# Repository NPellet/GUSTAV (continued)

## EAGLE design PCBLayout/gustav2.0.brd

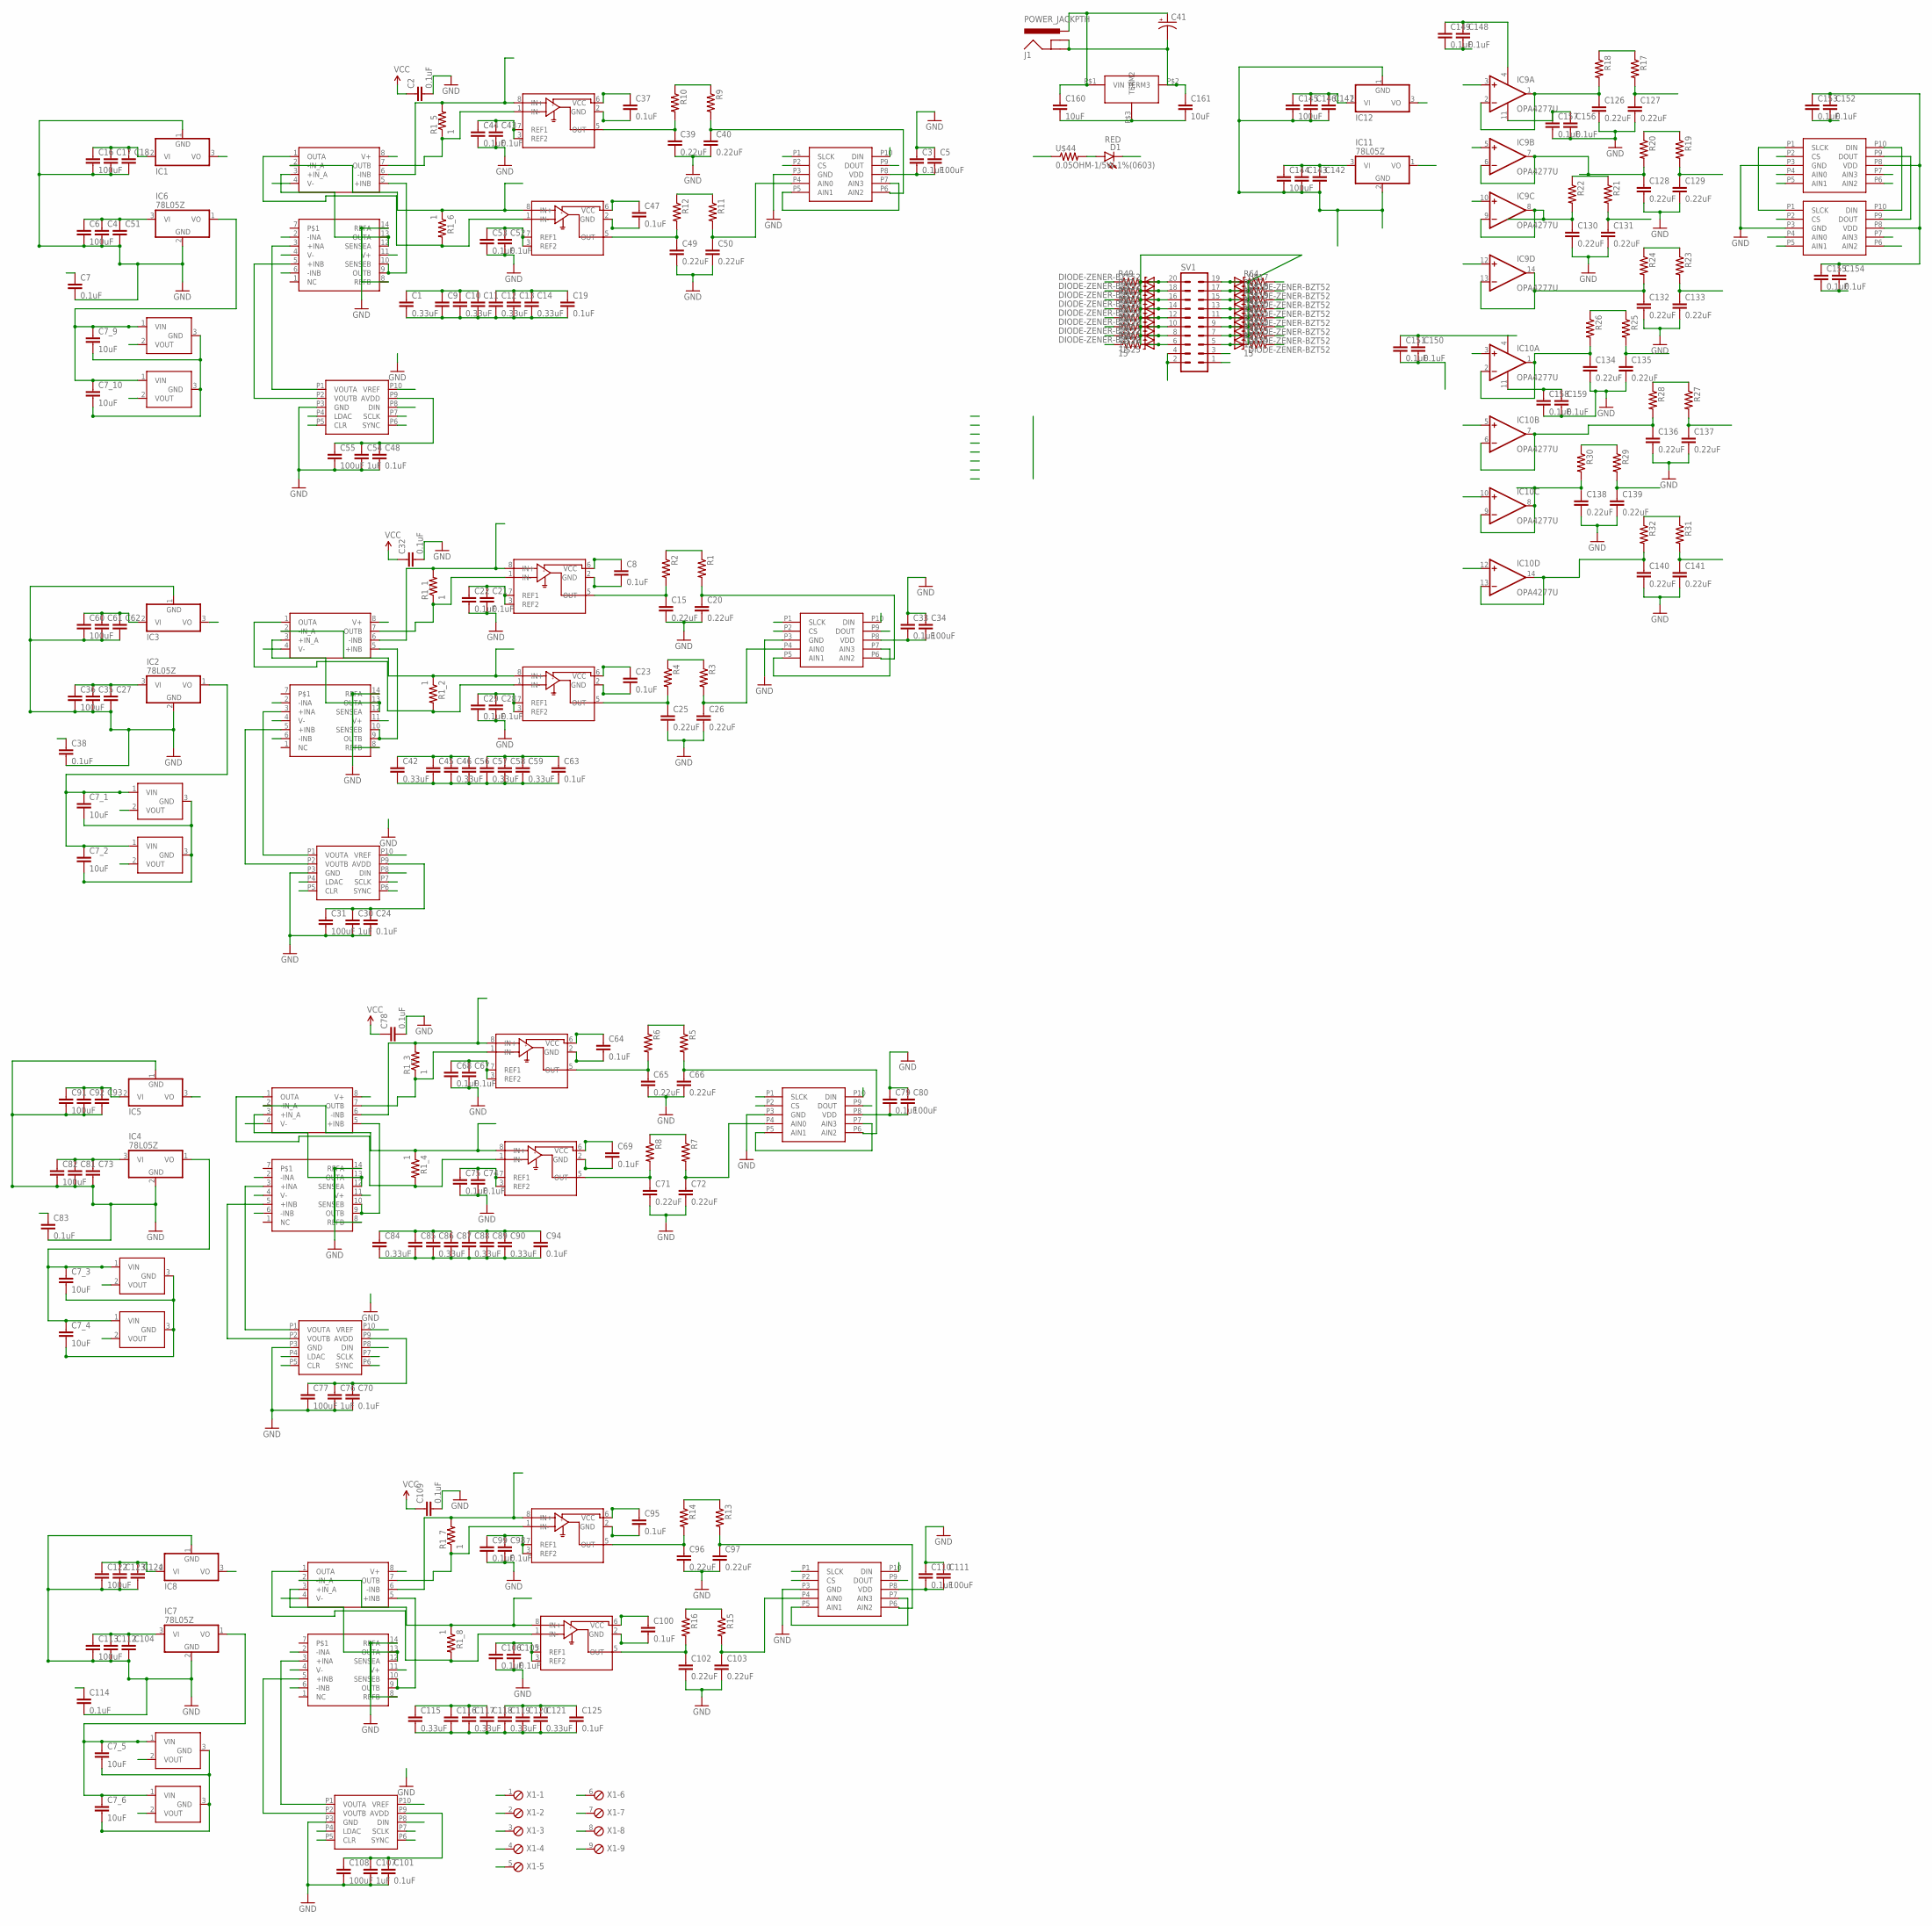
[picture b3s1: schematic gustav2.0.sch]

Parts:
C1, C10, C12, C14, C42, C46, C57, C59, C84, C86, C88, C90, C115, C117, C119, C121: 0.33uF; 0805-CAP
C2, C3, C7, C8, C19, C21, C22, C23, C24, C28, C29, C32, C33, C37, C38, C43, C44, C47, C48, C52, C53, C63, C64, C67, C68, C69, C70, C74, C75, C78, C79, C83, C94, C95, C98, C99, C100, C101, C105, C106, C109, C110, C114, C125, C148, C149, C150, C151, C152, C153, C154, C155, C156, C157, C158, C159: 0.1uF; 0603-CAP
C4, C9, C11, C13, C17, C18, C27, C35, C45, C51, C56, C58, C61, C62, C73, C81, C85, C87, C89, C92, C93, C104, C112, C116, C118, C120, C123, C124, C142, C143, C146, C147: CAP0603-CAP; 0603-CAP
C5, C6, C16, C31, C34, C36, C55, C60, C77, C80, C82, C91, C108, C111, C113, C122, C144, C145: 100uF; 1206-CAP
C7_1, C7_2, C7_3, C7_4, C7_5, C7_6, C7_9, C7_10, C160, C161: 10uF; 0603-CAP
C15, C20, C25, C26, C39, C40, C49, C50, C65, C66, C71, C72, C96, C97, C102, C103, C126, C127, C128, C129, C130, C131, C132, C133, C134, C135, C136, C137, C138, C139, C140, C141: 0.22uF; 0603-CAP
C30, C54, C76, C107: 1uF; 0603-CAP
C41: CAP_POLPTH1; CPOL-RADIAL-100UF-25V
D1: RED; LED-1206
IC1, IC3, IC5, IC8, IC12: 79L05Z; TO92
IC2, IC4, IC6, IC7, IC11: 78L05Z; TO92
IC9, IC10: OPA4277U; SO14
J1: POWER_JACKPTH; POWER_JACK_PTH
R1, R2, R3, R4, R5, R6, R7, R8, R9, R10, R11, R12, R13, R14, R15, R16, R17, R18, R19, R20, R21, R22, R23, R24, R25, R26, R27, R28, R29, R30, R31, R32: RESISTOR0603-RES; 0603-RES
R1_1, R1_2, R1_3, R1_4, R1_5, R1_6, R1_7, R1_8: 1; 0603-RES
R49, R50, R51, R52, R53, R54, R55, R56, R57, R58, R59, R60, R61, R62, R63, R64: 15; 0603-RES
REF1, REF2, REF3, REF4, REF5, REF6, REF3020, REF3040: REF3020; DBZ_R-PDSO-G3
SV1: ML20
U$1, U$5, U$13, U$35, U$41, U$42: ADS1018; S-PDSO-G10
U$2, U$10, U$16, U$38: INA2132REALONE; SO-14
U$3, U$12, U$34, U$40: DAC7563; S-PDSO-G10
U$4, U$11, U$33, U$39: LM7322; S-PDSO-G08-NOTHERMALPAD
U$6, U$7, U$8, U$9, U$14, U$15, U$36, U$37: INA285; SO-08
U$17, U$18, U$19, U$20, U$21, U$22, U$23, U$24, U$25, U$26, U$27, U$28, U$29, U$30, U$31, U$32: DIODE-ZENER-BZT52; SOD-323
U$43: TSRN; TSRN1
U$44: 0.05OHM-1/5W-1%(0603); 0603
X1: MPT9; 9POL254

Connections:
ADC: R53.1, U$5.P2 (CS)
ADC1: R52.1, U$1.P2 (CS)
ADC1_1: R63.1, SV1.17, U$18.2 (A)
ADC2_1: R61.1, SV1.13, U$20.2 (A)
ADC3: R54.1, U$13.P2 (CS)
ADC3_1: R59.1, SV1.9, U$22.2 (A)
ADC4: R55.1, U$35.P2 (CS)
ADC4_1: R57.1, SV1.5, U$24.2 (A)
ADCCS3: R57.2, U$42.P2 (CS)
ADCCS4: R56.1, U$41.P2 (CS)
ADCDIN: R62.2, U$1.P10 (DIN), U$5.P10 (DIN), U$13.P10 (DIN), U$35.P10 (DIN), U$41.P10 (DIN), U$42.P10 (DIN)
ADCDIN_1: R50.2, SV1.18, U$31.2 (A)
ADCDOUT: R50.1, U$1.P9 (DOUT), U$5.P9 (DOUT), U$13.P9 (DOUT), U$35.P9 (DOUT), U$41.P9 (DOUT), U$42.P9 (DOUT)
ADCDOUT_1: R51.2, SV1.16, U$30.2 (A)
ADSINA: C50.1, R11.2, U$1.P4 (AIN0)
ADSINA1: C26.1, R3.2, U$5.P4 (AIN0)
ADSINA2: C72.1, R7.2, U$13.P4 (AIN0)
ADSINA3: C103.1, R15.2, U$35.P4 (AIN0)
ADSINB: C40.1, R9.2, U$1.P6 (AIN2)
ADSINB1: C20.1, R1.2, U$5.P6 (AIN2)
ADSINB2: C66.1, R5.2, U$13.P6 (AIN2)
ADSINB3: C97.1, R13.2, U$35.P6 (AIN2)
CLK_1: R49.2, SV1.20, U$32.2 (A)
CLR: R51.1, U$3.P5 (CLR), U$12.P5 (CLR), U$34.P5 (CLR), U$40.P5 (CLR)
CLR_1: R54.2, SV1.10, U$27.2 (A)
D1: IC9.3 (+IN), R1_5.2, U$4.6 (-INB), U$7.8 (IN+), X1.2
D2: IC9.5 (+IN), R1_6.1, U$4.2 (-IN_A), U$8.8 (IN+), X1.1
D3: IC9.10 (+IN), R1_1.2, U$6.8 (IN+), U$11.6 (-INB), X1.4
D4: IC9.12 (+IN), R1_2.1, U$9.8 (IN+), U$11.2 (-IN_A), X1.3
D5: IC10.10 (+IN), R1_3.2, U$14.8 (IN+), U$33.6 (-INB), X1.7
D6: IC10.12 (+IN), R1_4.1, U$15.8 (IN+), U$33.2 (-IN_A), X1.6
D7: IC10.3 (+IN), R1_7.2, U$36.8 (IN+), U$39.6 (-INB), X1.9
D8: IC10.5 (+IN), R1_8.1, U$37.8 (IN+), U$39.2 (-IN_A), X1.8
DAC1: R61.2, U$3.P6 (SYNC)
DAC1_1: R64.1, SV1.19, U$17.2 (A)
DAC2: R60.2, U$12.P6 (SYNC)
DAC2_1: R62.1, SV1.15, U$19.2 (A)
DAC3: R59.2, U$34.P6 (SYNC)
DAC3_1: R60.1, SV1.11, U$21.2 (A)
DAC4: R58.2, U$40.P6 (SYNC)
DAC4_1: R58.1, SV1.7, U$23.2 (A)
GND: C1.2, C2.2, C3.1, C4.2, C5.1, C6.2, C7.2, C7_1.2, C7_2.2, C7_3.2, C7_4.2, C7_5.2, C7_6.2, C7_9.2, C7_10.2, C8.2, C9.2, C10.2, C11.2, C12.2, C13.2, C14.2, C15.2, C16.2, C17.2, C18.2, C19.2, C20.2, C21.2, C22.2, C23.2, C24.2, C25.2, C26.2, C27.2, C28.2, C29.2, C30.2, C31.2, C32.2, C33.1, C34.1, C35.2, C36.2, C37.2, C38.2, C39.2, C40.2, C41.2 (-), C42.2, C43.2, C44.2, C45.2, C46.2, C47.2, C48.2, C49.2, C50.2, C51.2, C52.2, C53.2, C54.2, C55.2, C56.2, C57.2, C58.2, C59.2, C60.2, C61.2, C62.2, C63.2, C64.2, C65.2, C66.2, C67.2, C68.2, C69.2, C70.2, C71.2, C72.2, C73.2, C74.2, C75.2, C76.2, C77.2, C78.2, C79.1, C80.1, C81.2, C82.2, C83.2, C84.2, C85.2, C86.2, C87.2, C88.2, C89.2, C90.2, C91.2, C92.2, C93.2, C94.2, C95.2, C96.2, C97.2, C98.2, C99.2, C100.2, C101.2, C102.2, C103.2, C104.2, C105.2, C106.2, C107.2, C108.2, C109.2, C110.1, C111.1, C112.2, C113.2, C114.2, C115.2, C116.2, C117.2, C118.2, C119.2, C120.2, C121.2, C122.2, C123.2, C124.2, C125.2, C126.2, C127.2, C128.2, C129.2, C130.2, C131.2, C132.2, C133.2, C134.2, C135.2, C136.2, C137.2, C138.2, C139.2, C140.2, C141.2, C142.2, C143.2, C144.2, C145.2, C146.2, C147.2, C148.2, C149.2, C150.2, C151.2, C152.2, C153.2, C154.2, C155.2, C156.2, C157.2, C158.2, C159.2, C161.1, D1.C, IC1.1 (GND), IC2.2 (GND), IC3.1 (GND), IC4.2 (GND), IC5.1 (GND), IC6.2 (GND), IC7.2 (GND), IC8.1 (GND), IC11.2 (GND), IC12.1 (GND), J1.GND, J1.GNDBREAK, REF1.3 (GND), REF2.3 (GND), REF3.3 (GND), REF4.3 (GND), REF5.3 (GND), REF6.3 (GND), REF3020.3 (GND), REF3040.3 (GND), SV1.2, SV1.4, U$1.P3 (GND), U$2.8 (REFB), U$2.14 (REFA), U$3.P3 (GND), U$5.P3 (GND), U$6.2 (GND), U$7.2 (GND), U$8.2 (GND), U$9.2 (GND), U$10.8 (REFB), U$10.14 (REFA), U$12.P3 (GND), U$13.P3 (GND), U$14.2 (GND), U$15.2 (GND), U$16.8 (REFB), U$16.14 (REFA), U$17.1 (C), U$18.1 (C), U$19.1 (C), U$20.1 (C), U$21.1 (C), U$22.1 (C), U$23.1 (C), U$24.1 (C), U$25.1 (C), U$26.1 (C), U$27.1 (C), U$28.1 (C), U$29.1 (C), U$30.1 (C), U$31.1 (C), U$32.1 (C), U$34.P3 (GND), U$35.P3 (GND), U$36.2 (GND), U$37.2 (GND), U$38.8 (REFB), U$38.14 (REFA), U$40.P3 (GND), U$41.P3 (GND), U$42.P3 (GND), U$43.P$2 (TERM3), X1.5
INAOUTB: C49.1, R12.2, U$8.5 (OUT)
INAOUTB1: C25.1, R4.2, U$9.5 (OUT)
INAOUTB2: C71.1, R8.2, U$15.5 (OUT)
INAOUTB3: C102.1, R16.2, U$37.5 (OUT)
INAOUTB4: C126.1, IC9.1 (OUT), IC9.2 (-IN), R18.2
INAOUTB5: C128.1, IC9.6 (-IN), IC9.7 (OUT), R20.2
INAOUTB6: C130.1, IC9.8 (OUT), IC9.9 (-IN), R22.2
INAOUTB7: C132.1, IC9.13 (-IN), IC9.14 (OUT), R24.2
INAOUTB8: C134.1, IC10.1 (OUT), IC10.2 (-IN), R26.2
INAOUTB9: C136.1, IC10.6 (-IN), IC10.7 (OUT), R28.2
INAOUTB10: C138.1, IC10.8 (OUT), IC10.9 (-IN), R30.2
INAOUTB11: C140.1, IC10.13 (-IN), IC10.14 (OUT), R32.2
INOUTA: C39.1, R10.2, U$7.5 (OUT)
INOUTA1: C15.1, R2.2, U$6.5 (OUT)
INOUTA2: C65.1, R6.2, U$14.5 (OUT)
INOUTA3: C96.1, R14.2, U$36.5 (OUT)
LDAC: R49.1, U$3.P4 (LDAC), U$12.P4 (LDAC), U$34.P4 (LDAC), U$40.P4 (LDAC)
LDAC_1: R53.2, SV1.12, U$28.2 (A)
unnamed: R3.1, R4.1
unnamed: U$2.9 (OUTB), U$2.10 (SENSEB), U$4.5 (+INB)
unnamed: U$10.9 (OUTB), U$10.10 (SENSEB), U$11.5 (+INB)
unnamed: R11.1, R12.1
unnamed: U$2.5 (+INB), U$3.P2 (VOUTB)
unnamed: U$2.12 (SENSEA), U$2.13 (OUTA), U$4.3 (+IN_A)
unnamed: U$10.12 (SENSEA), U$10.13 (OUTA), U$11.3 (+IN_A)
unnamed: R55.2, SV1.8, U$26.2 (A)
unnamed: R56.2, SV1.6, U$25.2 (A)
unnamed: U$10.5 (+INB), U$12.P2 (VOUTB)
unnamed: D1.A, U$44.2
unnamed: R7.1, R8.1
unnamed: U$16.9 (OUTB), U$16.10 (SENSEB), U$33.5 (+INB)
unnamed: U$16.12 (SENSEA), U$16.13 (OUTA), U$33.3 (+IN_A)
unnamed: U$16.5 (+INB), U$34.P2 (VOUTB)
unnamed: R15.1, R16.1
unnamed: U$38.9 (OUTB), U$38.10 (SENSEB), U$39.5 (+INB)
unnamed: U$38.12 (SENSEA), U$38.13 (OUTA), U$39.3 (+IN_A)
unnamed: U$38.5 (+INB), U$40.P2 (VOUTB)
unnamed: R17.1, R18.1
unnamed: R19.1, R20.1
unnamed: R21.1, R22.1
unnamed: R23.1, R24.1
unnamed: R25.1, R26.1
unnamed: R27.1, R28.1
unnamed: R29.1, R30.1
unnamed: R31.1, R32.1
OUTPUTA: R1_6.2, U$4.1 (OUTA), U$8.1 (IN-)
OUTPUTA1: R1_2.2, U$9.1 (IN-), U$11.1 (OUTA)
OUTPUTA2: R1_4.2, U$15.1 (IN-), U$33.1 (OUTA)
OUTPUTA3: R1_8.2, U$37.1 (IN-), U$39.1 (OUTA)
OUTPUTB: R1_5.1, U$4.7 (OUTB), U$7.1 (IN-)
OUTPUTB1: R1_1.1, U$6.1 (IN-), U$11.7 (OUTB)
OUTPUTB2: R1_3.1, U$14.1 (IN-), U$33.7 (OUTB)
OUTPUTB3: R1_7.1, U$36.1 (IN-), U$39.7 (OUTB)
REF1: C21.1, C22.1, C28.1, C29.1, REF1.2 (VOUT), U$5.P5 (AIN1), U$5.P7 (AIN3), U$6.3 (REF2), U$6.7 (REF1), U$9.3 (REF2), U$9.7 (REF1), U$10.2 (-INA), U$10.6 (-INB)
REF2: C43.1, C44.1, C52.1, C53.1, REF3020.2 (VOUT), U$1.P5 (AIN1), U$1.P7 (AIN3), U$2.2 (-INA), U$2.6 (-INB), U$7.3 (REF2), U$7.7 (REF1), U$8.3 (REF2), U$8.7 (REF1)
REF3: REF2.2 (VOUT), U$12.P10 (VREF)
REF4: REF3040.2 (VOUT), U$3.P10 (VREF)
REF5: C67.1, C68.1, C74.1, C75.1, REF3.2 (VOUT), U$13.P5 (AIN1), U$13.P7 (AIN3), U$14.3 (REF2), U$14.7 (REF1), U$15.3 (REF2), U$15.7 (REF1), U$16.2 (-INA), U$16.6 (-INB)
REF6: REF4.2 (VOUT), U$34.P10 (VREF)
REF7: C98.1, C99.1, C105.1, C106.1, REF5.2 (VOUT), U$35.P5 (AIN1), U$35.P7 (AIN3), U$36.3 (REF2), U$36.7 (REF1), U$37.3 (REF2), U$37.7 (REF1), U$38.2 (-INA), U$38.6 (-INB)
REF8: REF6.2 (VOUT), U$40.P10 (VREF)
SCLK: R64.2, U$1.P1 (SLCK), U$3.P7 (SCLK), U$5.P1 (SLCK), U$12.P7 (SCLK), U$13.P1 (SLCK), U$34.P7 (SCLK), U$35.P1 (SLCK), U$40.P7 (SCLK), U$41.P1 (SLCK), U$42.P1 (SLCK)
SDIN: R63.2, U$3.P8 (DIN), U$12.P8 (DIN), U$34.P8 (DIN), U$40.P8 (DIN)
SDIN_1: R52.2, SV1.14, U$29.2 (A)
SENSEA: C127.1, R17.2, U$41.P5 (AIN1)
SENSEB: C129.1, R19.2, U$41.P4 (AIN0)
SENSEC: C131.1, R21.2, U$41.P7 (AIN3)
SENSED: C133.1, R23.2, U$41.P6 (AIN2)
SENSEE: C135.1, R25.2, U$42.P7 (AIN3)
SENSEF: C137.1, R27.2, U$42.P6 (AIN2)
SENSEG: C139.1, R29.2, U$42.P5 (AIN1)
SENSEH: C141.1, R31.2, U$42.P4 (AIN0)
VCC: C4.1, C6.1, C27.1, C35.1, C36.1, C41.1 (+), C51.1, C73.1, C81.1, C82.1, C104.1, C112.1, C113.1, C142.1, C143.1, C144.1, C160.1, IC2.3 (VI), IC4.3 (VI), IC6.3 (VI), IC7.3 (VI), IC11.3 (VI), J1.PWR, SV1.3, U$43.P$1 (VIN), U$44.1
VCC-: C16.1, C17.1, C18.1, C60.1, C61.1, C62.1, C91.1, C92.1, C93.1, C122.1, C123.1, C124.1, C145.1, C146.1, C147.1, C160.2, C161.2, IC1.2 (VI), IC3.2 (VI), IC5.2 (VI), IC8.2 (VI), IC12.2 (VI), SV1.1, U$43.P$3 (TERM2)
VOUTA: U$2.3 (+INA), U$3.P1 (VOUTA)
VOUTA1: U$10.3 (+INA), U$12.P1 (VOUTA)
VOUTA2: U$16.3 (+INA), U$34.P1 (VOUTA)
VOUTA3: U$38.3 (+INA), U$40.P1 (VOUTA)
VREF: C1.1, C2.1, C3.2, C5.2, C7.1, C7_9.1, C7_10.1, C9.1, C10.1, C11.1, C37.1, C47.1, C48.1, C54.1, C55.1, IC6.1 (VO), REF3020.1 (VIN), REF3040.1 (VIN), U$1.P8 (VDD), U$2.11 (V+), U$3.P9 (AVDD), U$4.8 (V+), U$7.6 (VCC), U$8.6 (VCC)
VREF1: C7_1.1, C7_2.1, C8.1, C23.1, C24.1, C30.1, C31.1, C32.1, C33.2, C34.2, C38.1, C42.1, C45.1, C46.1, C56.1, IC2.1 (VO), REF1.1 (VIN), REF2.1 (VIN), U$5.P8 (VDD), U$6.6 (VCC), U$9.6 (VCC), U$10.11 (V+), U$11.8 (V+), U$12.P9 (AVDD)
VREF2: C7_3.1, C7_4.1, C64.1, C69.1, C70.1, C76.1, C77.1, C78.1, C79.2, C80.2, C83.1, C84.1, C85.1, C86.1, C87.1, IC4.1 (VO), REF3.1 (VIN), REF4.1 (VIN), U$13.P8 (VDD), U$14.6 (VCC), U$15.6 (VCC), U$16.11 (V+), U$33.8 (V+), U$34.P9 (AVDD)
VREF3: C7_5.1, C7_6.1, C95.1, C100.1, C101.1, C107.1, C108.1, C109.1, C110.2, C111.2, C114.1, C115.1, C116.1, C117.1, C118.1, IC7.1 (VO), REF5.1 (VIN), REF6.1 (VIN), U$35.P8 (VDD), U$36.6 (VCC), U$37.6 (VCC), U$38.11 (V+), U$39.8 (V+), U$40.P9 (AVDD)
VREF-: C12.1, C13.1, C14.1, C19.1, IC1.3 (VO), U$2.4 (V-), U$4.4 (V-)
VREF-1: C57.1, C58.1, C59.1, C63.1, IC3.3 (VO), U$10.4 (V-), U$11.4 (V-)
VREF-2: C88.1, C89.1, C90.1, C94.1, IC5.3 (VO), U$16.4 (V-), U$33.4 (V-)
VREF-3: C119.1, C120.1, C121.1, C125.1, IC8.3 (VO), U$38.4 (V-), U$39.4 (V-)
VREF-SENSE: C156.1, C157.1, C158.1, C159.1, IC9.11 (V-), IC10.11 (V-), IC12.3 (VO)
VREFSENSE: C148.1, C149.1, C150.1, C151.1, C152.1, C153.1, C154.1, C155.1, IC9.4 (V+), IC10.4 (V+), IC11.1 (VO), U$41.P8 (VDD), U$42.P8 (VDD)
_ADC1: R1.1, R2.1
_ADC2: R5.1, R6.1
_ADC3: R13.1, R14.1
_ADC5: R9.1, R10.1

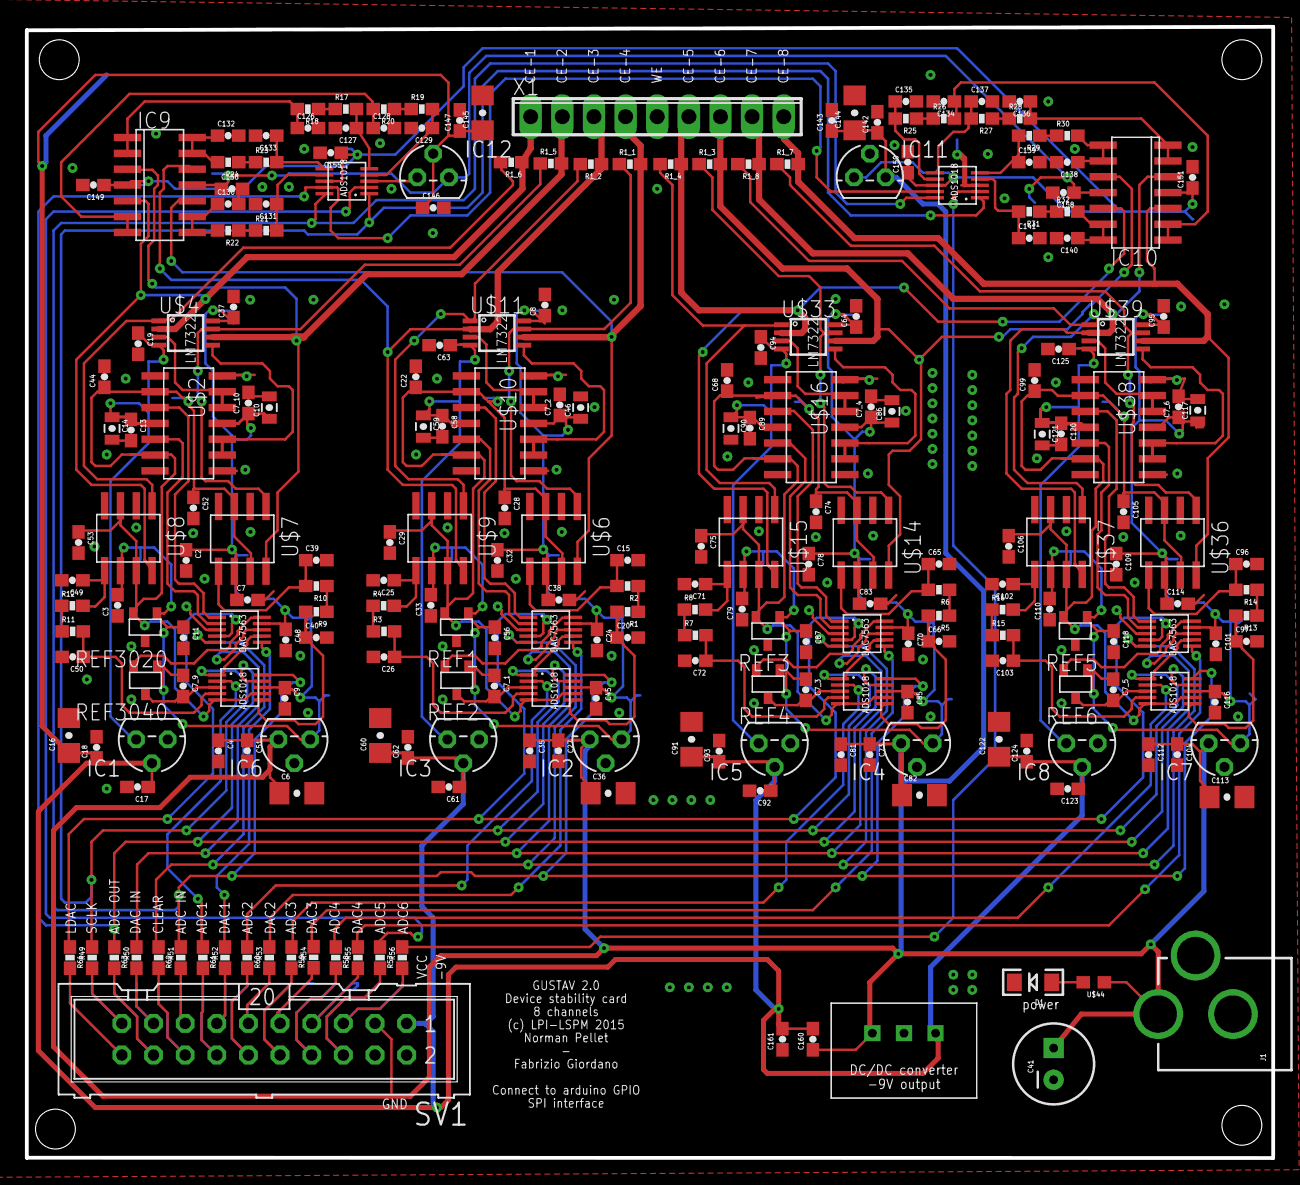
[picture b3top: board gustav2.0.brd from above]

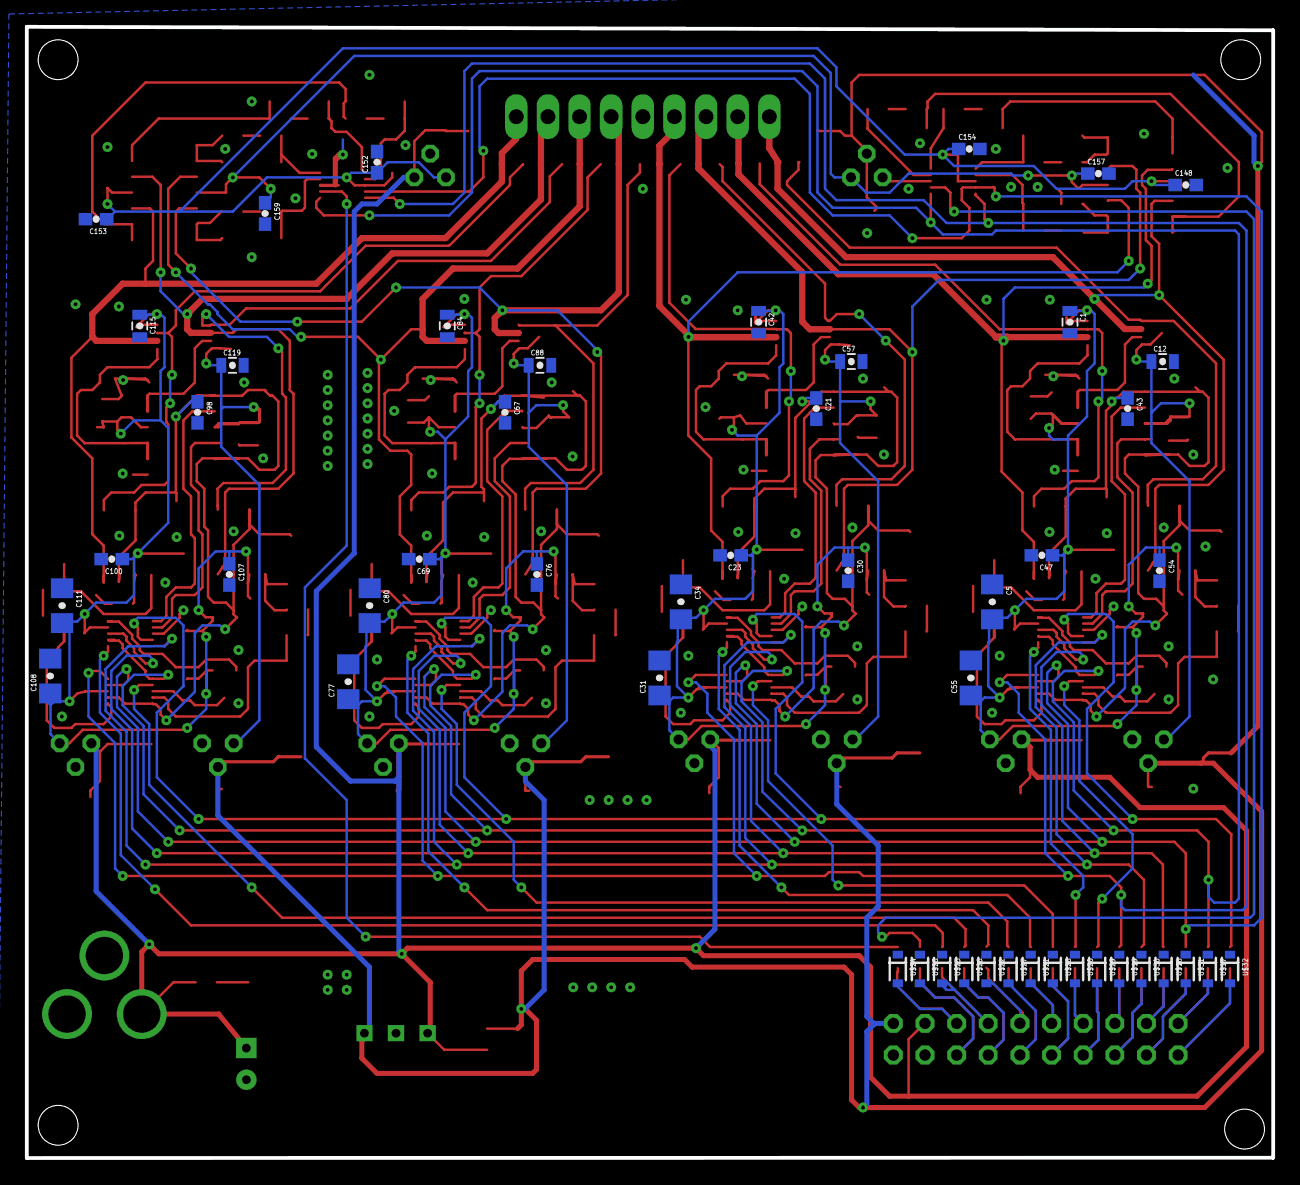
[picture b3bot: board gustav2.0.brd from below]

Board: 2 copper layers, 100.1 x 90.8 mm, 293 parts (50 on the bottom side), 134 nets.

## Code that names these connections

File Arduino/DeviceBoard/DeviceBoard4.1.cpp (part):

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#include "SPI.h"


#define LDAC 10
#define CLR 9
#define CS_DAC_0 8
#define CS_DAC_1 7
#define CS_DAC_2 6
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    configureDAC( 4 );
    configureDAC( 6 );
    
    pinMode( CLR, OUTPUT );
    pinMode( CS_DAC_0, OUTPUT );
    pinMode( CS_DAC_1, OUTPUT );
    pinMode( CS_DAC_2, OUTPUT );
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
unsigned int DeviceBoard::read( byte chan, byte mode ) {
    
    byte out1 = 0;
    byte out2 = 0;
    byte out3 = 0;
    byte out4 = 0;
    

    
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        }
    }
    
    out1 = 0;
    out2 = 0;
    out3 = 0;
    out4 = 0;
    byte in1, in2, in3, in4;
    
    
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
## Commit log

2015-12-18 Update project
2016-02-02 Rev2.0
2016-02-10 Add all files
2016-03-04 Add some MPPT files
2016-03-04 Add PCB + Arduino files
2016-03-09 Update MPPT
2016-03-12 MPP Update
2016-03-22 Update MPP
2016-04-07 Update APP
2016-04-07 Update multi commands
2016-09-28 Major update
2016-09-28 Add git ignore
2016-09-28 Remove some log and fix package.json deps
2016-09-28 Fix gitignore
2016-09-28 Add GUSTAV 4 board
2016-09-28 Rename calib file
2016-10-06 Fix minor bugs with data uploading
2016-10-18 Add download button
2016-10-18 Add list results interaction
2016-10-18 Fix list results backend
2016-10-18 Add influx server get measurements
2016-10-18 Add mask in UI
2016-10-18 Add get data feature
2016-10-18 Add export feature
2016-10-18 Fix app.js
2016-10-19 Fix data export
2016-10-19 Latest arduino libraries
2016-10-19 Latest arduino main
2016-12-22 Update all
2017-01-18 Fix bug induced by InfluxSQL data request
2017-03-09 Fix for new influxdb version and optimized jsGraph
